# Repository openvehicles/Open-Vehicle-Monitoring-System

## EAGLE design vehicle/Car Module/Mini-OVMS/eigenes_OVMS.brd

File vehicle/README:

Open Vehicle Monitoring System

The Car Module

The car module is the hard part. We require an extremely reliable and low-power module to fit in the car.
While it is relatively simple for a hobbyist to create one of these, the hard part is making a common
platform that a group of hobbyists can get behind, and to make it very high quality. Home-soldered
connections and US$100k electric cars don't go well together.

What we've done is take the foundational work done by fuzzy logic and others, to build a base platform module.
We've then negotiated with factories in China (we live just over the border in Hong Kong) to get this
professionally built.

The module plugs into the car DIAG port, which provides both power and a CAN bus connection that the module
can transmit/receive messages on.

The platform itself is based on a PIC18F2680 processor and SIMCOM GSM module. Factory built and assembled,
but based on an open source extendable architecture. You can either buy these modules pre-built, or build
your own. Any profits on the sale of hardware will got to charity.

The SIMCOM GSM module has the ability to send/receive SMS messages, as well as a built-in IP stack for
GPRS communication. It allows the module to talk both communication protocols with very little PIC software
required. We decided to use these modules (rather than USB modems) for reliability reasons, as well as
the SIMCOM built-in support for IP protocol.

The final version re-works the CPU+CAN board to be rectangular and fit as a plug-in piggy-back on the
SIMCOM module we've sourced. We've also re-worked the board layout to separate the CAN bus across a
cicuit-board divide (to keep the CAN signals very simple and physically separated from the rest of the
components). In the final version, we also extend the unused I/O pins of the CPU out on expansion pins
(to allow for such things as in-vehicle displays). It all fits in a small case, is extremely low power,
and has two LEDs for diagnostics and a windscreen / rear window stick-on GSM antenna for optimal
reception. Overall, the design is very elegant and extremely robust.

The in-car module can be configured to just be a passive listener on the CAN bus, but can also be an
active participant and transmit control messages onto the bus. It can even just relay CAN bus messages
over the Internet to the Server/App. It is very flexible and has enough RAM and ROM to do some interesting things.

Users can either follow the schematics to build their own compatible boards, or buy them pre-made from us.
We expect to be able to charge just US$99+shipping for pre-assembled in-car modules (the CPU+CAN controller
module, SIMCOM GSM module, car DIAG cable, housing box and GSM antenna). This is a non-profit endeavor,
with any profits inadvertently made being donated to charity.

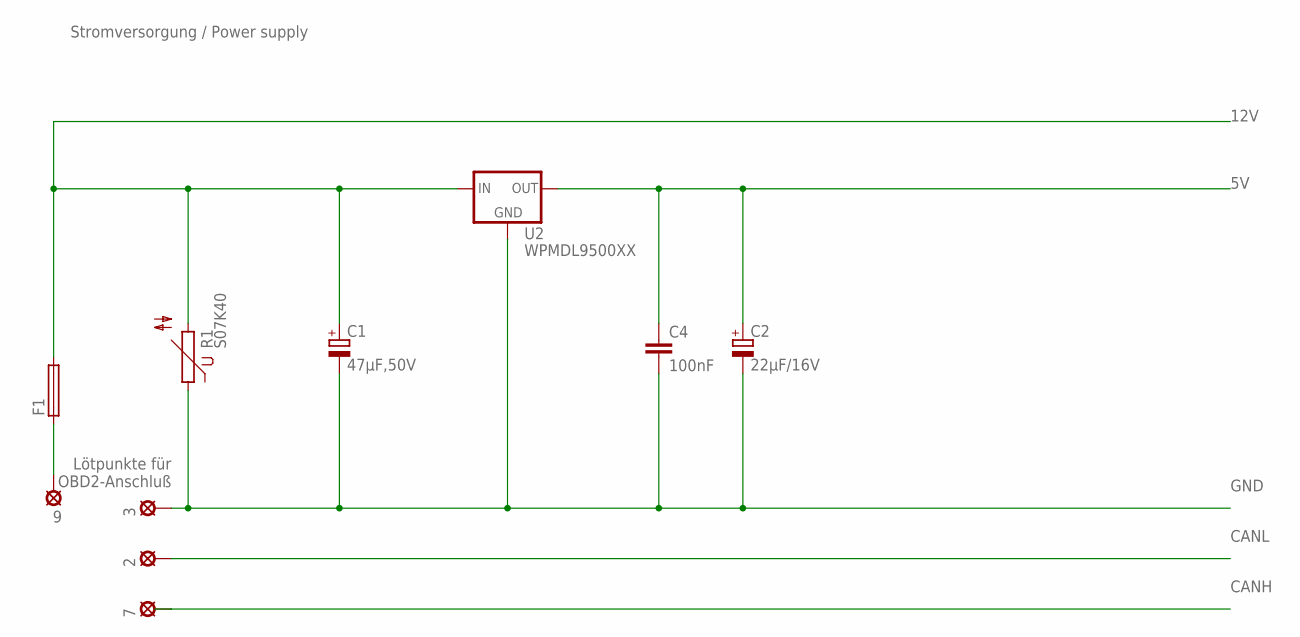
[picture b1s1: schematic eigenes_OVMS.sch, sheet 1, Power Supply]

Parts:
2, 3, 7, 9: LSP10
C1: 47µF,50V; E2,5-7
C2: 22µF/16V; E2,5-5
C4: 100nF; C025-025X050
F1: 19559
R1: S07K40
U2: WPMDL9500XX; WPMDL9500

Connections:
5V: C2.+, C4.1, U2.OUT; also elsewhere on the board
12V: C1.+, F1.2, R1.2, U2.IN; also elsewhere on the board
CANH: 7.MP; also elsewhere on the board
CANL: 2.MP; also elsewhere on the board
GND: 3.MP, C1.-, C2.-, C4.2, R1.1, U2.GND; also elsewhere on the board
unnamed: 9.MP, F1.1

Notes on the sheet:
Lötpunkte für OBD2-Anschluß
Stromversorgung / Power supply

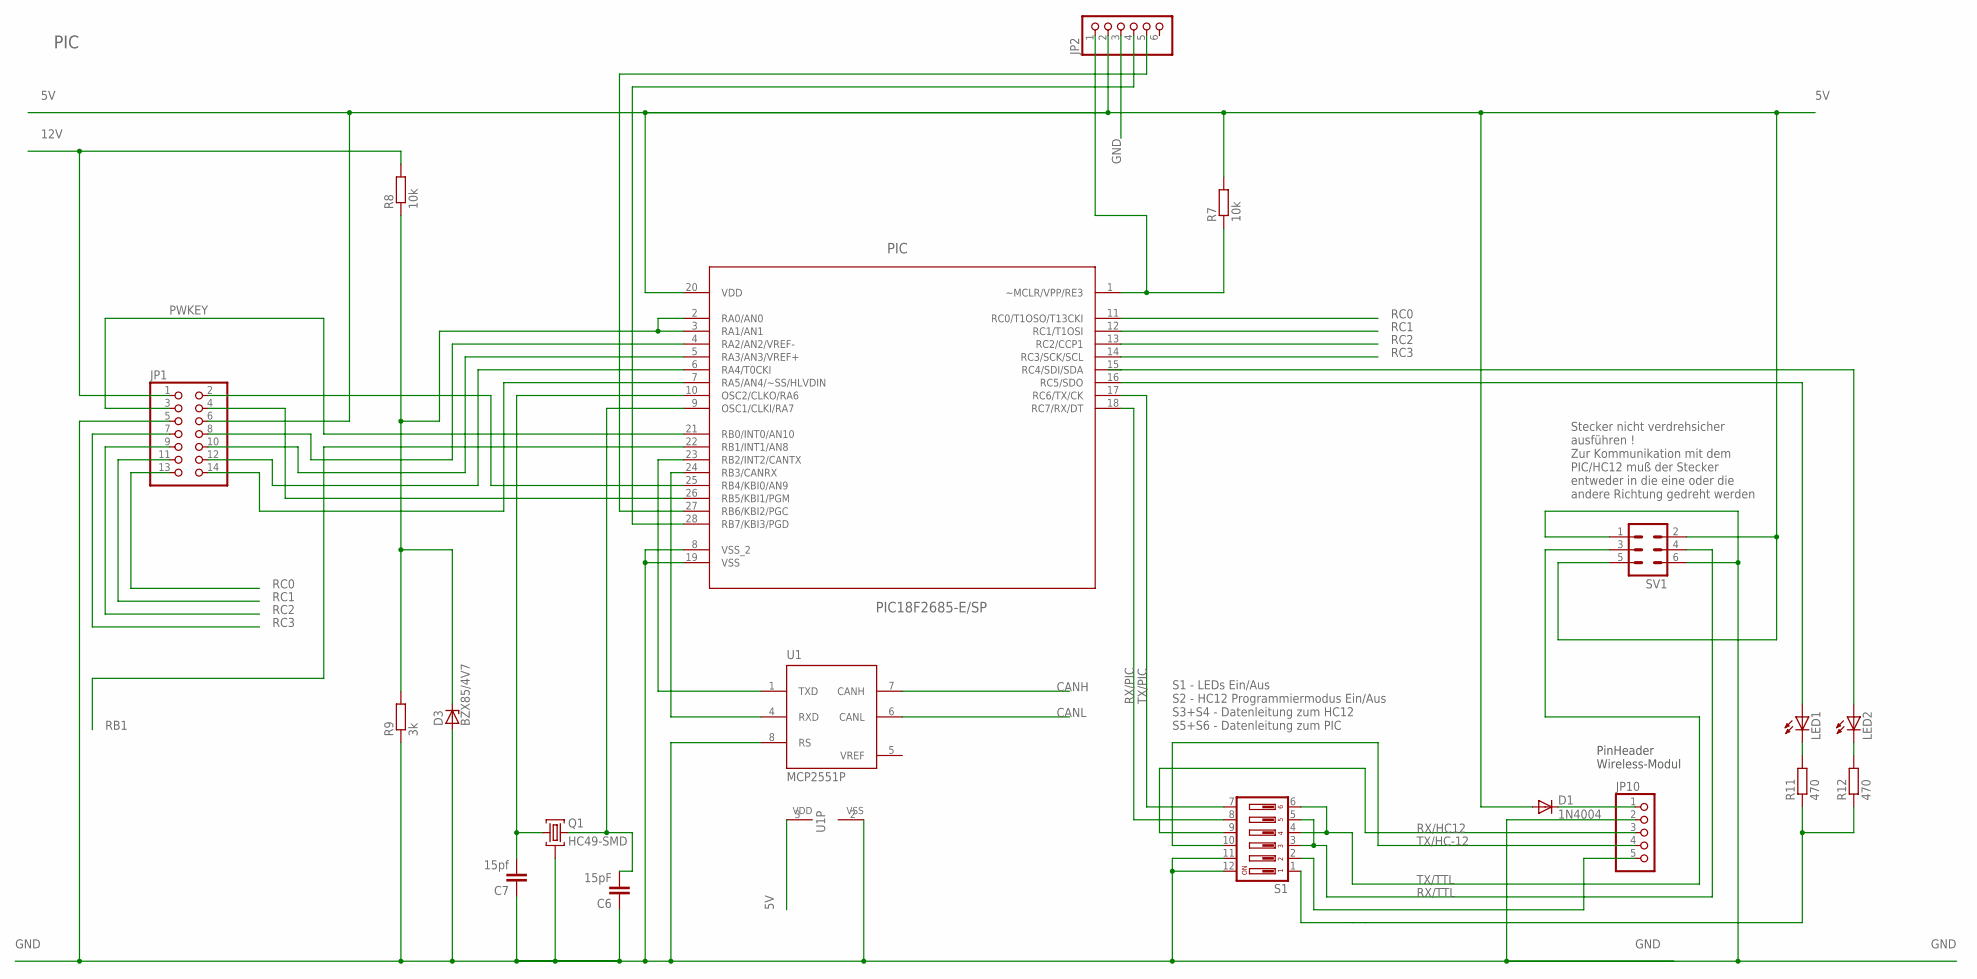
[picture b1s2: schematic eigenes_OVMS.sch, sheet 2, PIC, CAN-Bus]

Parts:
C6: 15pF; C025-025X050
C7: 15pf; C025-025X050
D1: 1N4004; DO41-10
D3: BZX85/4V7; DO41Z10
JP1: PINHD-2X7; 2X07
JP2: PINHD-1X6; 1X06
JP10: PINHD-1X5; 1X05
LED1, LED2: LED3MM
PIC: PIC18F2685-E/SP; DIP254P762X508-28
Q1: HC49-SMD; HC49U
R7, R8: 10k; 0207/7
R9: 3k; 0207/7
R11, R12: 470; 0207/7
S1: DIP06YL
SV1: ML6L
U1: MCP2551P; DIL8

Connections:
5V: D1.A, JP1.6, JP2.2, PIC.20 (VDD), R7.2, SV1.2, SV1.5, U1.3 (VDD); also elsewhere on the board
12V: JP1.1, R8.2; also elsewhere on the board
CANH: U1.7 (CANH); also elsewhere on the board
CANL: U1.6 (CANL); also elsewhere on the board
GND: C6.1, C7.1, D3.A, JP1.5, JP2.3, JP10.2, PIC.8 (VSS_2), PIC.19 (VSS), Q1.2, R9.1, S1.11, S1.12, SV1.1, SV1.6, U1.2 (VSS), U1.8 (RS); also elsewhere on the board
unnamed: JP2.1, PIC.1 (~MCLR/VPP/RE3), R7.1
unnamed: C7.2, PIC.10 (OSC2/CLKO/RA6), Q1.1
unnamed: C6.2, PIC.9 (OSC1/CLKI/RA7), Q1.3
unnamed: PIC.23 (RB2/INT2/CANTX), U1.1 (TXD)
unnamed: PIC.24 (RB3/CANRX), U1.4 (RXD)
unnamed: LED2.A, PIC.15 (RC4/SDI/SDA)
unnamed: LED1.A, PIC.16 (RC5/SDO)
unnamed: JP2.4, PIC.28 (RB7/KBI3/PGD)
unnamed: JP2.5, PIC.27 (RB6/KBI2/PGC)
unnamed: JP1.8, PIC.4 (RA2/AN2/VREF-)
unnamed: JP1.10, PIC.5 (RA3/AN3/VREF+)
unnamed: JP1.12, PIC.6 (RA4/T0CKI)
unnamed: D1.C, JP10.1
unnamed: LED1.K (C), R11.2
unnamed: LED2.K (C), R12.2
unnamed: R11.1, R12.1, S1.1
unnamed: JP1.14, PIC.7 (RA5/AN4/~SS/HLVDIN)
unnamed: JP10.5, S1.2
PWKEY: JP1.3, PIC.21 (RB0/INT0/AN10)
RA1: D3.C, PIC.2 (RA0/AN0), PIC.3 (RA1/AN1), R8.1, R9.2
RB1: PIC.22 (RB1/INT1/AN8); also elsewhere on the board
RB4: JP1.2, PIC.25 (RB4/KBI0/AN9)
RB5: JP1.4, PIC.26 (RB5/KBI1/PGM)
RC0: JP1.13, PIC.11 (RC0/T1OSO/T13CKI)
RC1: JP1.11, PIC.12 (RC1/T1OSI)
RC2: JP1.9, PIC.13 (RC2/CCP1)
RC3: JP1.7, PIC.14 (RC3/SCK/SCL)
RX/HC12: JP10.3, S1.9
RX/PIC: PIC.18 (RC7/RX/DT), S1.8
RX/TTL: S1.3, S1.5, SV1.4
TX/HC-12: JP10.4, S1.10
TX/PIC: PIC.17 (RC6/TX/CK), S1.7
TX/TTL: S1.4, S1.6, SV1.3
VREF: U1.5 (VREF)

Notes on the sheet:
PinHeader Wireless-Modul
S1 - LEDs Ein/Aus S2 - HC12 Programmiermodus Ein/Aus S3+S4 - Datenleitung zum HC12 S5+S6 - Datenleitung zum PIC
Stecker nicht verdrehsicher ausführen ! Zur Kommunikation mit dem PIC/HC12 muß der Stecker entweder in die eine oder die andere Richtung gedreht werden
PIC

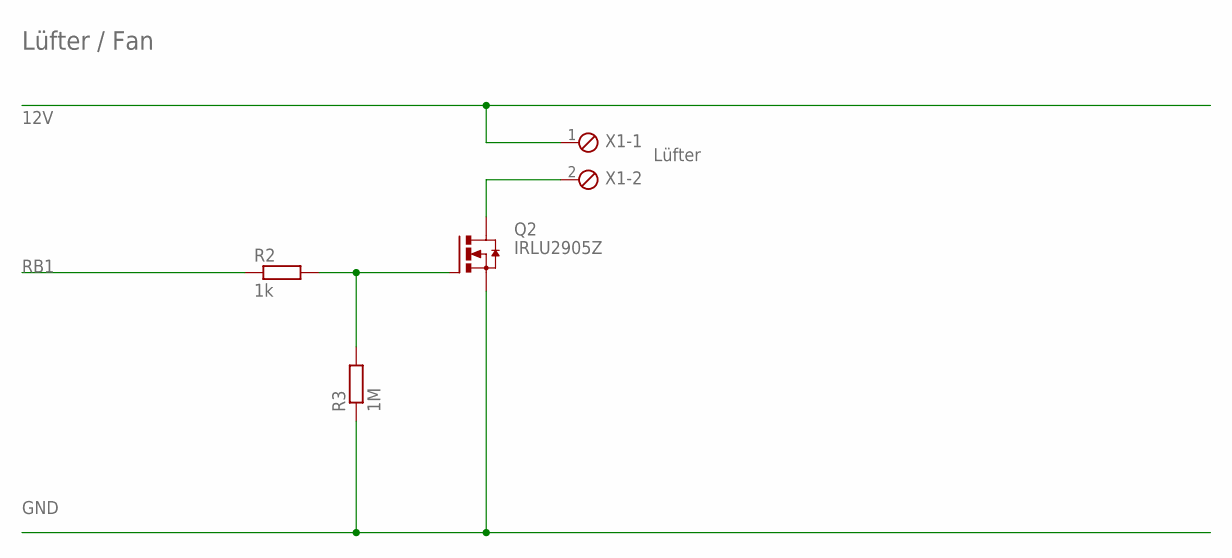
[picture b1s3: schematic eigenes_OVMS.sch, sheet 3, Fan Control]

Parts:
Q2: IRLU2905Z; TO251AA-V
R2: 1k; 0207/7
R3: 1M; 0207/7
X1: MPT2; 2POL254

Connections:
12V: X1.1; also elsewhere on the board
GND: Q2.3 (S), R3.1; also elsewhere on the board
unnamed: Q2.1 (G), R2.2, R3.2
unnamed: Q2.2 (D), X1.2
RB1: R2.1; also elsewhere on the board

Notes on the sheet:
Lüfter
Lüfter / Fan

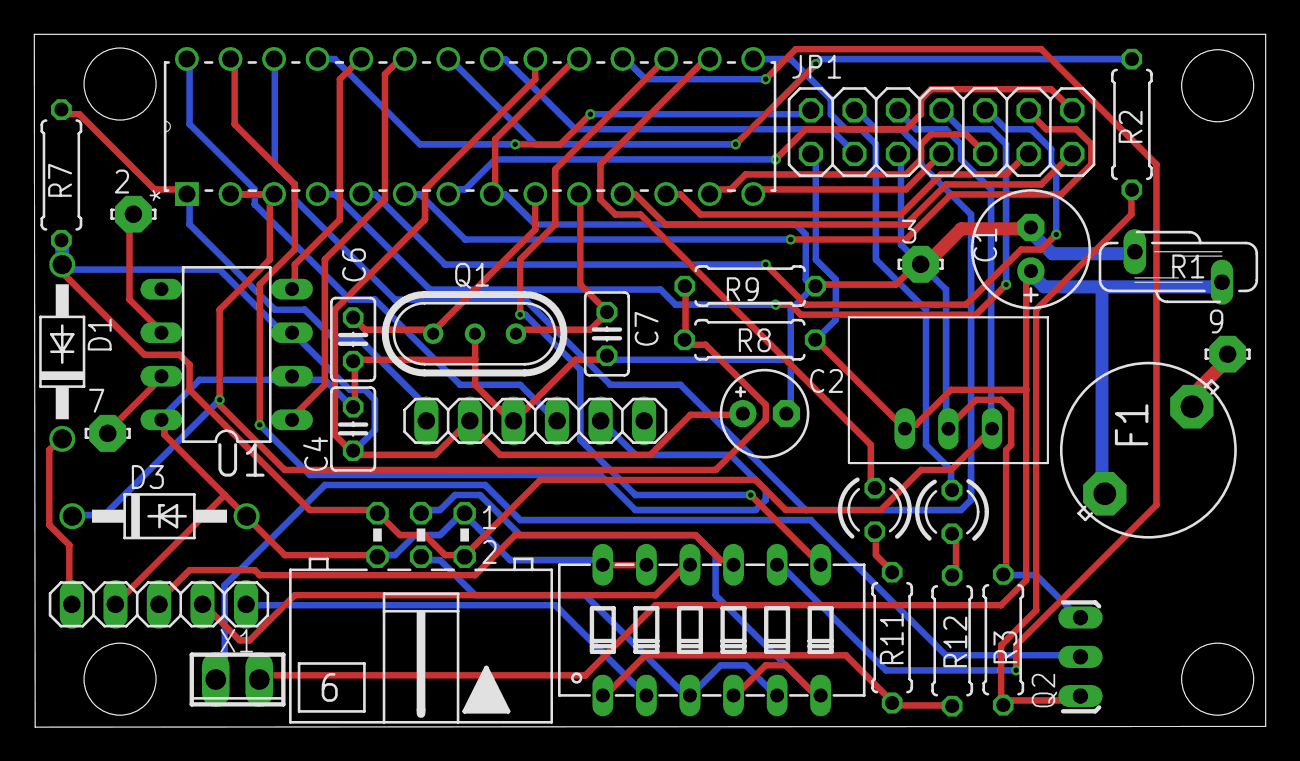
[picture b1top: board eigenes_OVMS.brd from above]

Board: 2 copper layers, 71.8 x 40.4 mm, 33 parts (0 on the bottom side), 41 nets.

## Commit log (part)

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2013-10-15 CTP returns -1 invalid chgMode, -2 wAvail <= 0, -3 imEnd<=imStart
2013-10-16 V1_TeslaRoadster config: remove diag, include acc
2013-10-20 ACC: Charge port klduges for Tesla Roadster
2013-10-22 ACC: Use car_chargesubstate!=0x07 instead of pilot signal
2013-10-25 ACC: Delay CTP calculations until acc charge mode is stable
2013-10-28 Config changes for 2.5.5 release
2013-10-29 Server: work in progress for logging to db
2013-10-30 Update vehicle_thinkcity.c
    Added fix for stale temp in app (car_doors3bits.CoolingPump= (car_stale_temps<=1)?0:1; )
2013-11-02 Fixed typo
2013-11-02 Label this as 2.6.1
2013-11-05 Server: tr.vece: 1426=HVAC: High current pump failure
2013-11-11 Added charge alert when interrupted, 80% and when done
2013-11-20 - add params to vehicle_minutestocharge - add #define for charge voltage assumed by ACC - add CTP SMS command - add timestamp to STAT SMS command - generalize timestring_to_mins - TR: CTP uses CAC100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
2013-11-21 OBDII: Implementation using new vehicle polling framework
2013-12-17 - add stp_date to print the date associated with given timestamp - add datestring_to_timestamp to convert GSM CCLK string to timestamp
2013-12-17 Request, and sync, GSM time
2013-12-30 Twizy: Major update: SEVCON controller configuration !HIGHLY EXPERIMENTAL FEATURE! read documentation (userguide) first!
    ATT: due to ROM limitations, this release cannot be
    combined with other vehicles and/or DIAG mode!
2014-01-02 - CAN simulator preprocessor flag renamed to OVMS_CANSIM - Read/write SDO: retries + watchdog clearing - Power map generator for SPEED / TORQUE - TORQUE command extended by max motor power parameter 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
2014-01-08 OVMS_POLLER configs
2014-01-10 Twizy: 2 minor documentation fixes
2014-01-18 Twizy V3.1.2: access to SEVCON logs / monitoring - new command: MSG 209 = CMD_ResetLogs - new command: MSG 210 = CMD_QueryLogs - active faults log included with fault alert - added Twizy client scrip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
    Common:
    - moved client scripts to separate directory
2014-01-19 Call vehicle_idlepoll() and vehicle_ticker10th() in delay100b() - but with recursion protection
2014-01-19 2.6.2 firmware .hex builds
2014-01-21 Fixed speed bug for miles configured cars
2014-01-26 - Twizy 3.1.3 documentation
2014-01-27 Optimization of interrupt function
2014-02-03 ACC: Route MSG commands through to ACC (for possible special handling)
2014-03-10 2.6.5 Firmware
2014-05-01 remove temp testing code
2014-05-07 Revision to SOC and idealrange calculations, from Tom Saxtons suggestions
2014-06-02 UTILS: cr2lf() now also translates '^' to '/' (SIM908 SMS charset workaround)
2014-06-21 Twizy release 3.3.0: - Lock/Unlock/Valet mode support - Homelink = profile switch - Speed limit below default reverse speed also limits reverse
2014-07-03 - SMS "GPRS?" tells about GPRS switch status - SMS "HOMELINK", "LOCK", "UNLOCK", "VALET" & "UNVALET" may now be called without parameters
2014-07-26 Dont close chargeport in stat message handler
2014-07-26 v2.6.6
2014-08-27 Add tr vece 1533
2014-10-19 Dont use net_msg_cmd_msg in vehicle mode, instead use msg, to allow sms messages to issue commands
2014-10-19 Allow ACC acc_handle_msg to choose to handle a particular message
2014-10-23 Comments regarding 104.8576ms timer1
2014-12-08 Setting acc params, without location, when not in a location, leads to off-by-one index parameter write
2015-01-26 Update ovms_server_tr.vece
    I synced the error code list to the Roadster Wiki @ TMC.
2015-03-17 - Documentation: Modem / network state machine diagram
2015-03-21 - Framework: ETR vars & STAT msg extended by separate range/SOC estimates + max ideal range - Twizy: support car_chargeduration & framework chargetime ETR variables
2015-03-28 - Twizy: FAQ update
2015-04-12 Twizy firmware 3.5.2: - STAT odometer output precision 10th km/mi - Reset battery monitor on charge start - Battery monitor MTU optimization (RT-BAT-P/C messages) - GPS log extended by twizy_status -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
    - Twizy docs: added german GPS visualization howto
2015-06-24 Twizy version 3.5.3 - CA? SMS output extended by charge status - CFG TSMAP rework to avoid "Param dyn range" alert - OP mode after profile switch: 5 tries with 100 ms timeout
    Framework:
    - Fix for MSG SMS wrapper result translation
2015-07-23 - Added client script to retrieve server log
2015-08-19 Twizy: added howto on using the module for diag/tuning without a SIM card
2015-08-23 One of multiple apps disconnect fix
2015-08-24 Twizy: - Fixed auto power calculations for default minprc values - Changed auto recup level to scale levels configured - car_SOC no longer rounded to avoid 99.5% == 100% - Trip end odometer saved & u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
2015-09-21 Added documentation contribution: Twizy workshop (german) by Peter Saß (www.M4DM3N.de)
2015-09-23 Require car_time for vehicle_track.c
2015-09-23 Make COPS more lenient. Support GPRS DNS.
2015-09-23 2.8.1 changes
2015-10-03 Twizy: - Script client update for new RT-PWR-Log record format - CAN object dictionary update (battery power -> current) - User guide update for release 3.6 - Powermap calculator update for auto powe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
2015-10-07 New vehicle: Kia Soul EV, initial version 0.1 (alpha/untested) - VIN, car status, doors & charging status, SOC, estimated range, speed
2015-10-16 Kia Soul: - SOC/range CAN data validation - OBDII polling clarification
2015-10-19 Kia Soul: - ISR optimization - OBD diag data init & length debugging
2015-11-05 QRY-function
    Added QRY-function + a few minor changes.
2015-11-13 0.32 - Added data from onboard charger and VMCU
    Added motor and MCU temperatures, rewrote handling of Car on, car off,
    port open.
    Added time to full charge (initial version)
2015-11-16 - doc: CPAN SSL info
2015-11-23 v0.41 Pollstates, cleanups and car_hargekWh
2015-11-29 v0.43 TRIP-sms and ambient temperature
    // 0.43 26 Nov 2015 (Geir Øyvind Vælidalo)
    // - Fixed trip in AVG sms + added discharge and recuperation for last
    trip.
    // - Changed AVG-sms to TRIP-sms
    // - Added ambient temperature
    // - MaxRange is adjusted based on ambient temp and assumes half range
2015-12-09 Add hints on 0x100/0x96 and 0x400/0x01
2015-12-20 - Added compiler switch OVMS_NO_CRASHDEBUG
2015-12-26 - Twizy user manual update (V3.7)
2016-01-04 - Server: send Google push notifications also while App is connected
2016-01-10 - cmd.pl: timeout handling changed to IO::Socket::Timeout to allow operation within web server environments - cmd.pl: added resultcnt option to speed up execution - cfgconv: added tags (key=value) fo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
2016-02-27 MPLABX 3.1x support, and OVMS_BUILDCONFIG to show selected build config in version strings
2016-03-01 Added files via upload
    Added new Documentation for Kia Soul EV
2016-03-13 Twizy 3.7.2: - Fix: "CA?" outputs ETR SOC if ETR range is zero - CAN control bits to disable emergency reset, kickdown & autopower
2016-03-14 v2.8.5 label
2016-04-04 Twizy user guide v1.8 (BMS power limit bypass)
2016-04-15 Twizy documentation: - Added command overview - Added limiter designer to powermap calculator - Added some more registers to SDO list
2016-05-14 Leaf: extract gids out to a separate value
2016-05-14 Leaf: - use presence of ABS messages to indicate driving - add some TODO
2016-05-14 Leaf: extract car on-off to a function
2016-05-15 Deterministic TRISC & PORTC init in each module
2016-05-19 Merged Kia Soul 0.46 06 Mar 2016 (Geir Øyvind Vælidalo)
2016-05-25 - SIM808 GPS fetch & coordinate processing - "GPS?" command optimized GM link, extended by OSM link
2016-05-29 v2.8.6 production builds
2016-06-01 Leaf: extract CAN transmit to vehicle_nissanleaf_sendCanMessage
2016-06-01 Leaf: initial remote climate control, only works during charging
2016-06-01 Leaf: support for remote charging
2016-06-03 Leaf: send remote command 25 times like the Gen 2 does
2016-07-06 - New framework compiler flags: a) OVMS_FIXED_DIAGMODE = always enter DIAG mode on startup b) OVMS_DIAGDATA = enable data output to DIAG port
    - Twizy: OVMS_DIAGDATA showcase: output some status data in ticker1
    - Twizy: HELP cmd extensions excluded by default to save ROM space
    use flag OVMS_TWIZY_HELP to enable
2016-07-31 Framework: - Message "S": chargekwh in 1/10 kWh, added chargepower & battvoltage
    Server:
    - Added chargetype, chargepower & battvoltage to HTTP API
    Twizy:
    - Trip report also gives SOC difference if positive
    - Added car_chargepower (at battery) & car_battvoltage
    - car_chargecurrent now set from current battery charge current
2016-09-20 Leaf: accept all frames into poll1, decode battery voltage and current and abuse charger line voltage and current to expose
2016-10-22 - Twizy firmware builds V2.8.8/RT3.7.3
2016-11-13 - Added annotated PCB image to SimpleConsole howto
2016-11-24 - Twizy 3.8.1 documentation updates
2016-12-06 - Added speed & trip length to location update (msg L) - Added b4 + substate to JSON API - Fixed spelling of 'charge_etr_range' in JSON API
2016-12-19 - fixed potential buffer overrun in par_get() - fixed potential buffer overrun in net_poll() - fixed net_poll() read timeout - removed superfluous delays - removed ENV notification kludge
2016-12-31 - status.pl: added option to retrieve update from car instead server
2017-01-03 - Addendum to last commit
2017-01-04 Move NissanLeaf and Mitsubishi from Experimental to Production builds
2017-01-07 Server: - Fix for APNS active connection check - Logging also logins, errors & terminations to database
2017-01-07 - Firmware builds updated - Added builds update script
2017-01-14 - Added car_soh to server & docs
2017-01-19 Nissan Leaf: decode speed
2017-01-21 Nissan Leaf: Report Quick Charging correctly
2017-02-04 improved SIM908 GPS data
2017-03-19 Framework: - Avoid min SOC trigger from BMS SOC correction at charge start
    Twizy:
    - 12V current level correction
    - Added SMS cmd "CA H" (halt charging) and supporting MSG CMD_StopCharge
    - Changed charge done detection from SOC 100% to power level 0
2017-05-05 - Zoe added to Readme
2017-05-31 - SimpleConsole optimized scheme & PCB layout & sample pics Contribution by "Balu-Baer" H. Bols <balu-baer@t-online.de>
2017-06-06 Logo files
2017-06-18 - Fix: CAN ISR hardened against missing/late hooks - Vehicles: init of unused filters to avoid random IRQ triggers
2017-06-24 Framework 3.1.4: - Refined GPS lock into fix mode & satellite count - Added GPS lock info to GPS? command - Added GSM signal quality to GPRS? command - Refactored argument tokenizing into utils.c, re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
    - Twizy: fixed CAN TXREQ polling
2017-08-25 Nissan Leaf: Configurable SOC calculation
2017-08-26 - Diag mode init fix
2017-08-26 Twizy firmware builds for V3.8.4a
2017-08-27 Nissan Leaf: decode ambient temperature
2017-08-27 Firmware build update for Nissan Leaf V1.3
2017-08-29 Nissan Leaf: turn off remote climate control if the car turns on
2017-10-22 Nissan Leaf: Gen2 Charger support
2017-12-16 Server: forward push notification type to email channel
2018-08-09 Twizy: reset battery alerts & watches on new max stddev level
2018-10-23 ovms_shell for v2 servers
2019-05-02 Twizy 3.9.1: generate regenerative braking signal on port RB5, updated user guide
2019-08-21 Server: log level config & refinement, statistics logging fixed
2019-10-16 Ignore DMC push alert messages
2019-10-24 Move clients to https://github.com/openvehicles/Open-Vehicle-Server.git
